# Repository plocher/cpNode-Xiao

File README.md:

## cpNode Xiao

cpNodes are Arduino-ecosystem nodes created by Model Railroad Control Systems'
for the Computer Model Railroad Interface (CMRI) system.

The Xiao variations by SPCoast use the ESP32 family of
microcontrollers, and communicate with each other and with
classic C/MRI nodes via CMRInet.  These controllers also support
WiFi and Bluetooth for future protocol development.

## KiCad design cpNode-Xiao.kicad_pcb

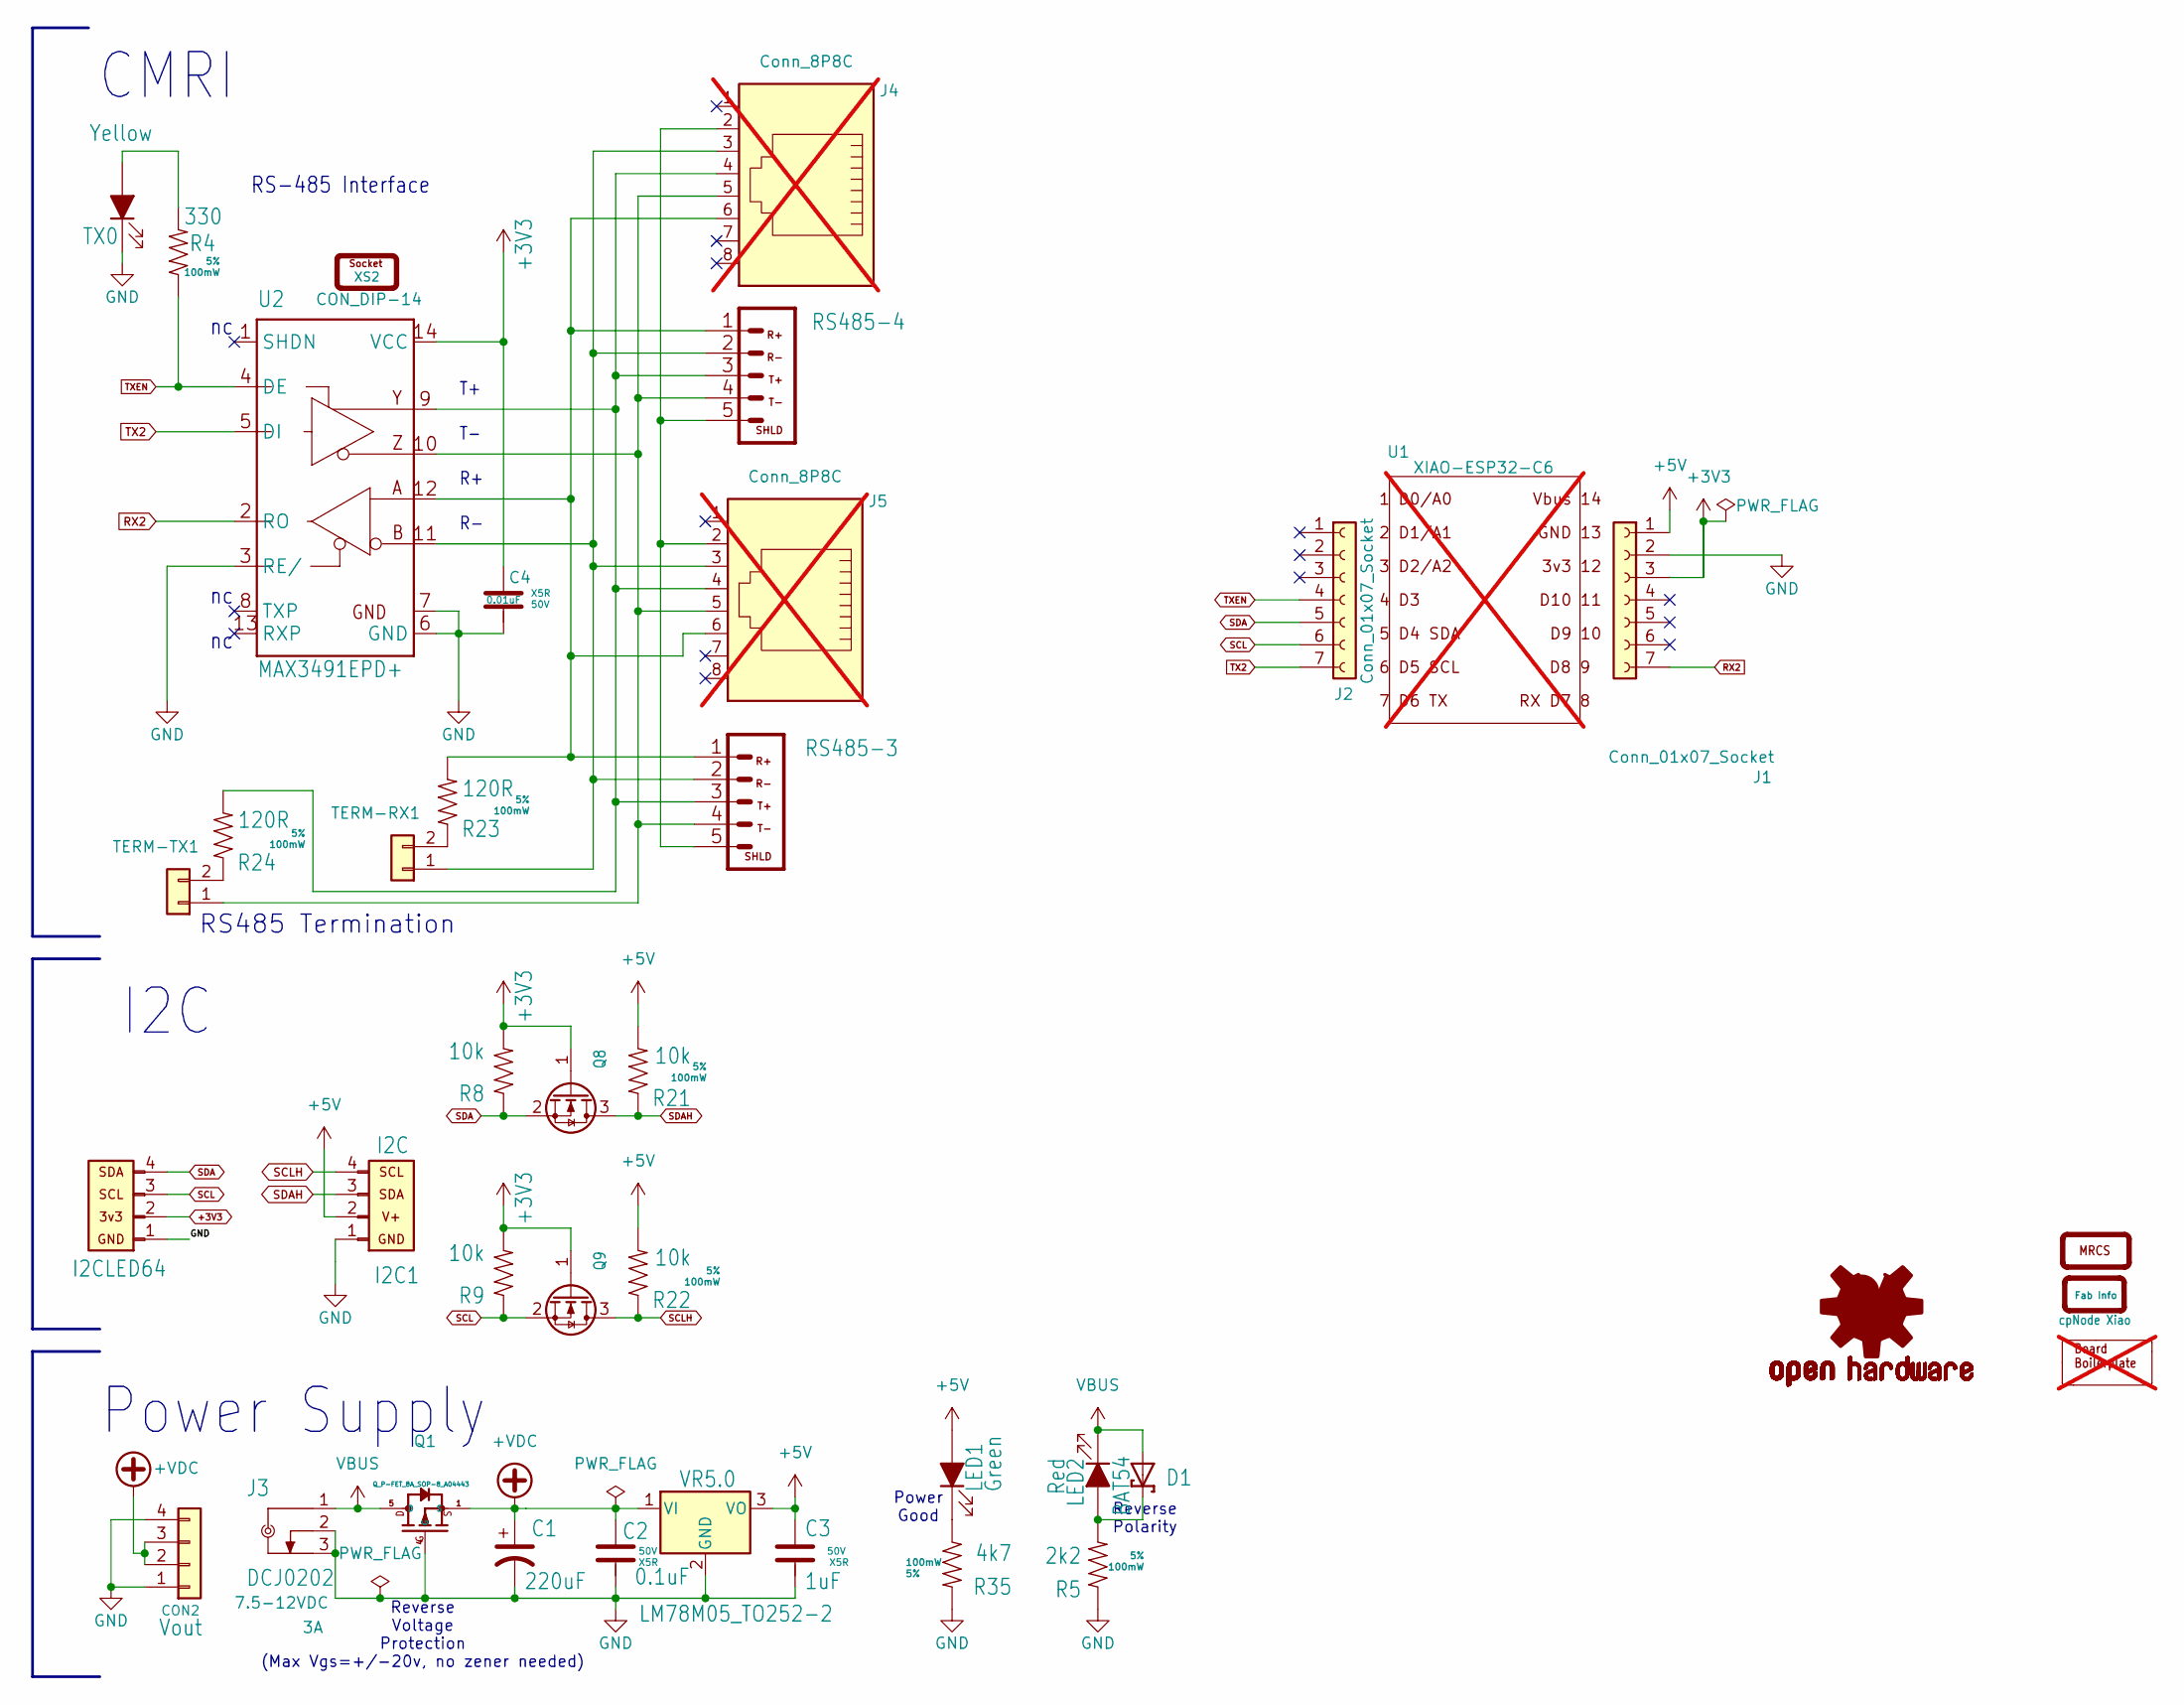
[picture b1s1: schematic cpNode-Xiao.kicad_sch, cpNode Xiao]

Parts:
BOARD0: Board_068x80; not fitted
C1: 220uF; CP_Elec_8x10
C2: 0.1uF; 0603-CAP; Voltage 50V
C3: 1uF; 0603-CAP; Voltage 50V
C4: 0.01uF; 0603-CAP; Voltage 50V
CON2: Vout; Connector_01x04_V; LCSC C2691448
D1: BAT54; TSOT-23
DOC1: ${TITLE}; SILK_BoardID
I2C1: I2C; Connector_I2C-0.100_R; LCSC C2691448
I2CLED64: I2C-OLED; Connector_I2C-OLED
J1, J2: Conn_01x07_Socket; PinSocket_1x07_P2.54mm_Vertical
J3: DCJ0202; BarrelJack_Kycon_KLDX-0202-xC_Horizontal; Voltage 7.5-12VDC
J4, J5: Conn_8P8C; RJ45_OST_PJ012-8P8CX_Vertical; LCSC C7205130; not fitted
LED1: Green; 0603-LED
LED2: Red; 0603-LED
MRCS1: MRCS; SILK_Logo-MRCS
OSHW1: OSHW; SILK_Label-OSHW
Q1: Q_P-FET_8A_SOP-8_A04443; HTSOP-8-1EP_3.9x4.9mm_P1.27mm_EP2.4x3.2mm
Q8, Q9: BSS138; SOT-23
R4: 330; 0603-RES; Tolerance 5%
R5: 2k2; 0603-RES; Tolerance 5%
R8, R9, R21, R22: 10k; 0603-RES; Tolerance 5%
R23, R24: 120R; 0603-RES; Tolerance 5%
R35: 4k7; 0603-RES; Tolerance 5%
RS485-3, RS485-4: CON_1x-5-3.5-screw; Connector_01x05_V-CMRINET-3.5MM
TERM-RX1: Conn_01x02; Connector_01x02_V
TERM-TX1: Conn_01x02; Connector_01x02_V
TX0: Yellow; 0603-LED
U1: XIAO-ESP32-C6; not fitted
U2: MAX3491EPD+; CERDIP-14_W7.62mm_SideBrazed
VR5.0: LM78M05_TO252-2; TO-252-2; LCSC C347278
XS2: CON_DIP-14; XS-DIP14

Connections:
+3V3: C4.1, I2CLED64.2, J1.3, Q8.1 (G), Q9.1 (G), R8.2, R9.2, U2.14 (VCC)
+5V: C3.1, I2C1.2, J1.1, LED1.2 (A), R21.2, R22.2, VR5.0.3 (VO)
+VDC: C1.1, C2.1, CON2.2, CON2.3, Q1.1 (S), Q1.2 (S), Q1.3 (S), VR5.0.1 (VI)
GND: C1.2, C2.2, C3.2, C4.2, CON2.1, CON2.4, I2C1.1, I2CLED64.1, J1.2, J3.2, J3.3, Q1.4 (G), R5.1, R35.2, TX0.1 (K), U2.3 (RE/), U2.6 (GND), U2.7 (GND@1), VR5.0.2 (GND)
unnamed: D1.3 (C), LED2.2 (A), R5.2
unnamed: J4.2, J5.2, RS485-3.5, RS485-4.5
unnamed: LED1.1 (K), R35.1
unnamed: J4.3, J5.3, RS485-3.2, RS485-4.2, TERM-RX1.1, U2.11 (B)
unnamed: R23.1, TERM-RX1.2
unnamed: J4.5, J5.5, RS485-3.4, RS485-4.4, TERM-TX1.1, U2.10 (Z)
unnamed: R24.1, TERM-TX1.2
unnamed: R4.2, TX0.2 (A)
unnamed: J4.6, J5.6, R23.2, RS485-3.1, RS485-4.1, U2.12 (A)
unnamed: J4.4, J5.4, R24.2, RS485-3.3, RS485-4.3, U2.9 (Y)
RX2: J1.7, U2.2 (RO)
SCL: I2CLED64.3, J2.6, Q9.2 (S), R9.1
SCLH: I2C1.4, Q9.3 (D), R22.1
SDA: I2CLED64.4, J2.5, Q8.2 (S), R8.1
SDAH: I2C1.3, Q8.3 (D), R21.1
TX2: J2.7, U2.5 (DI)
TXEN: J2.4, R4.1, U2.4 (DE)
VBUS: D1.1 (A), J3.1, LED2.1 (K), Q1.5 (D), Q1.6 (D), Q1.7 (D), Q1.8 (D), Q1.9 (D)

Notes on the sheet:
I2C
Reverse Voltage Protection (Max Vgs=+/-20v, no zener needed)
RS-485 Interface
RS485 Termination
Power Good
CMRI
Power Supply
Reverse Polarity

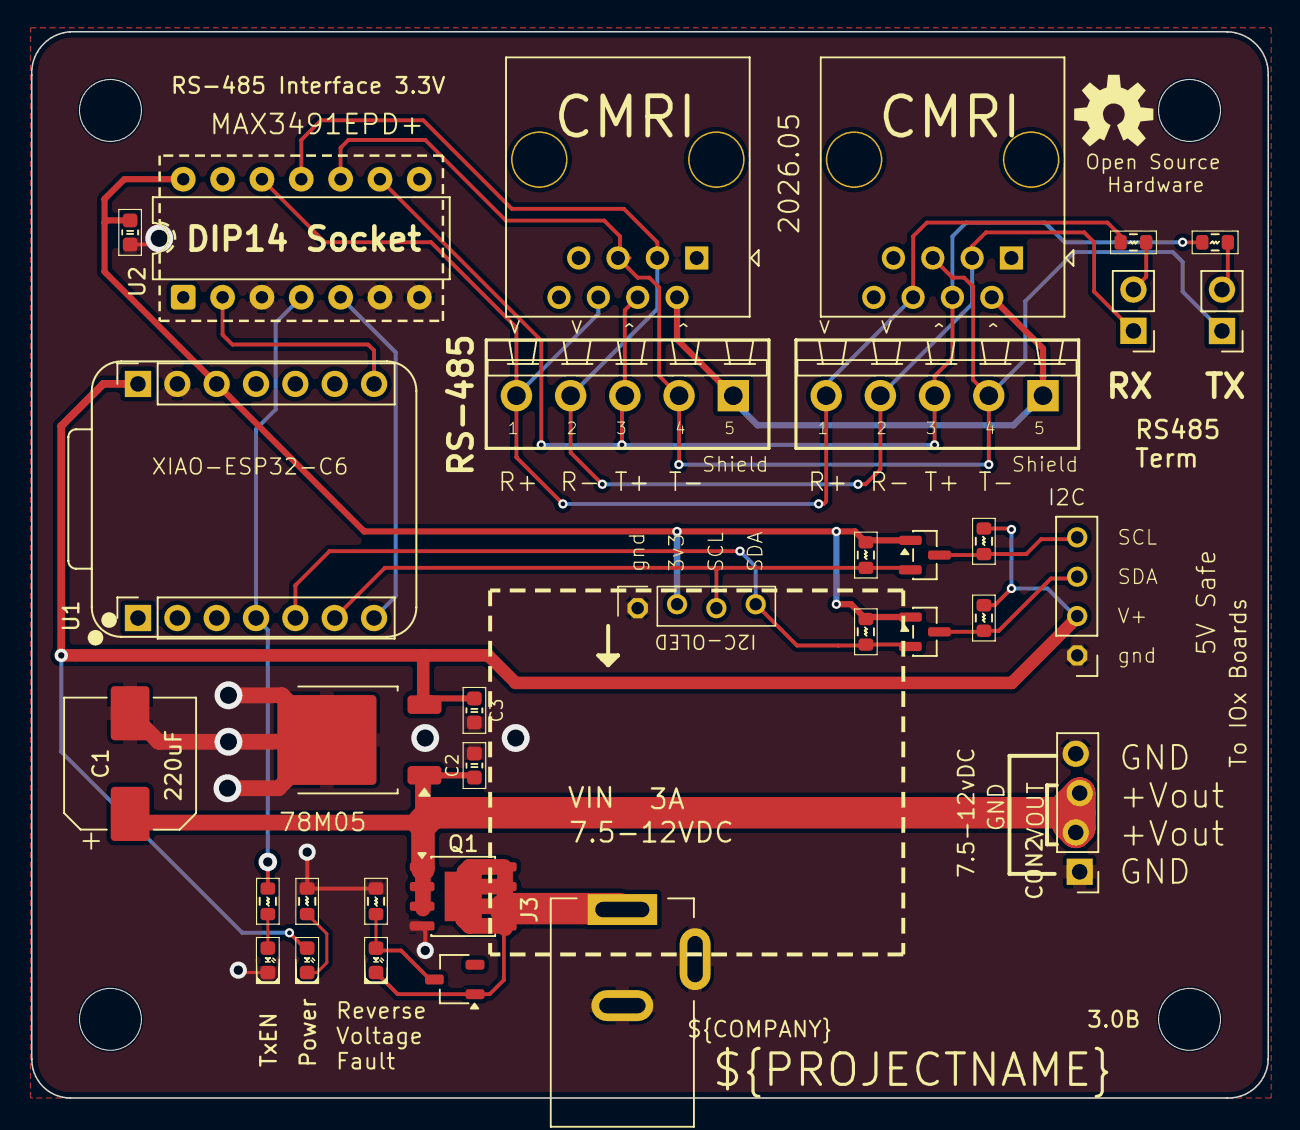
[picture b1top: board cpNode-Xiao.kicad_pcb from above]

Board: 2 copper layers, 79.8 x 68.8 mm, 40 parts (1 on the bottom side), 22 nets.
